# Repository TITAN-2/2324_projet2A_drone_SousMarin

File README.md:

# Projet de Drone Sous-marin - TITAN II - 2e Année ENSEA

## Description du Projet

Ce projet de deuxième année d'école d'ingénieur en électronique informatique vise à concevoir et développer un drone sous-marin contrôlable à distance. L'objectif de ce projet est de récupérer des objets dans le fond de l'étang de Cergy : plus précisement des lunettes de plongée. 
Le drone sera équipé de deux moteurs submersibles afin de propulser l'ensemble sous l'eau, de différents capteurs explicités plus tard, de seringues en guise de ballast, et finalement d'une STM32 couplée a une Raspeberry Pi. 

Le drone sera équipé de capteurs de pression et d'une centrale inertielle, connectés à une carte STM32. La communication entre les capteurs, les moteurs et les utilisateurs sera gérée par la STM32, tandis qu'une Raspberry Pi sera utilisée pour recevoir les informations des utilisateurs, héberger un serveur, et afficher une interface homme-machine (IHM) avec un flux vidéo provenant des caméras Pi.

## Fonctionnalités Principales

1. **STM32 pour la Gestion des Capteurs et des Moteurs**
   - La carte STM32 sera responsable de la communication avec les capteurs.
   - Elle assurera également le contrôle des moteurs en réponse aux commandes des utilisateurs.

2. **Raspberry Pi pour l'Interface Utilisateur**
   - La Raspberry Pi recevra les informations des utilisateurs.
   - Elle hébergera un serveur qui affichera le flux vidéo des caméras Pi et permettra aux utilisateurs d'envoyer des commandes au drone sous-marin.

3. **UART STM32 et la Raspberry Pi**
   - L'UART sera bidirectionnel
   - La Rasberry communiquera vers la STM32 les commandes utilisateurs reçu du serveur.
   - La STM32 communiquera vers la Raspberry les informations des différents capteurs (position, vitesse, niveau de batterie...)

## Configuration Matérielle

- **STM32**
  - Pin A0: PWM Moteur Gauche
  - Pin A1: PWM Moteur Droit
  - Pin RX: Reception de l'UART Raspberry
  - Pin TX: Transmission via UART vers Raspberry

- **Raspberry Pi**
  - A définir

- **Caméras Pi**
  - Voir le HowTo (a définir également)

## Installation et Exécution

1. Cloner le dépôt du projet sur la machine hôte.
   ```bash
   git clone https://github.com/votre-utilisateur/projet-drone-sous-marin.git
## Tester les parties indépendemments

[LA RECEPTION STM32](/RECEPTION_UART_H7A3ZIQ/HOWTO.md)

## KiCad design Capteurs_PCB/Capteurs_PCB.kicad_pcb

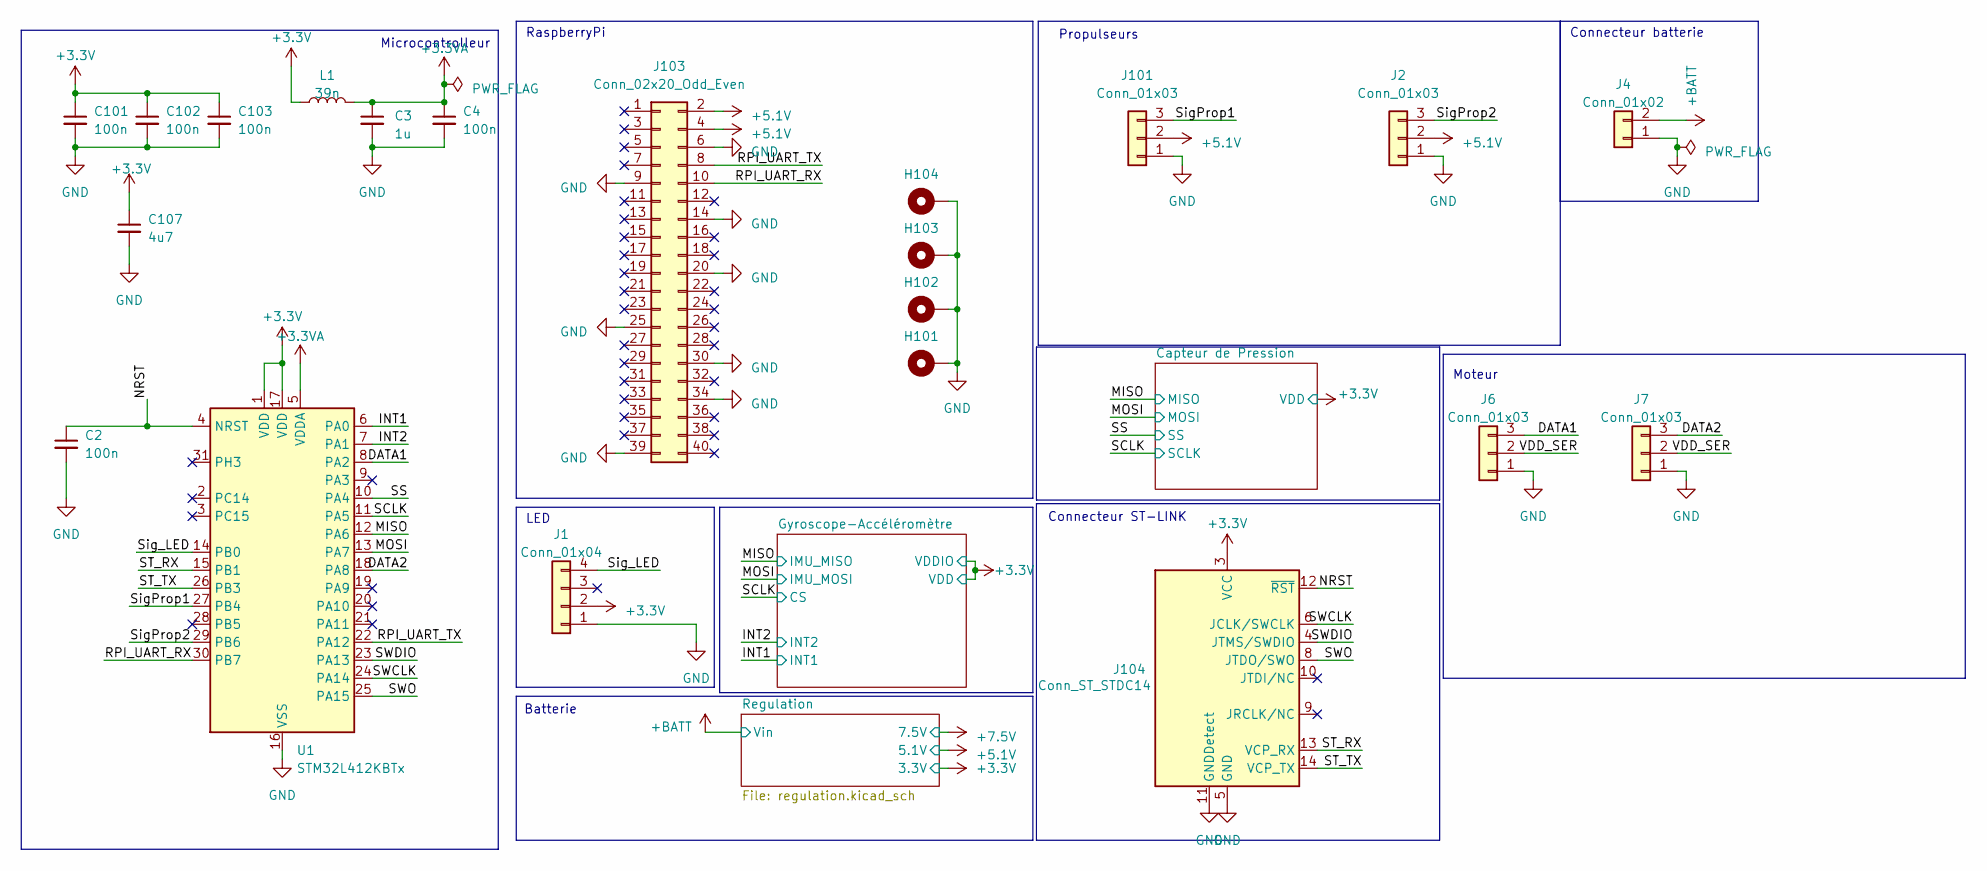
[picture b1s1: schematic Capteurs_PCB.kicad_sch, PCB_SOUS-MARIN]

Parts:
C2, C4, C101, C102, C103: 100n; C_0603_1608Metric_Pad1.08x0.95mm_HandSolder
C3: 1u; C_0603_1608Metric_Pad1.08x0.95mm_HandSolder
C107: 4u7; C_0603_1608Metric_Pad1.08x0.95mm_HandSolder
H101, H102, H103, H104: MountingHole_Pad; MountingHole_3.2mm_M3_DIN965_Pad
J1: Conn_01x04; JST_XH_B4B-XH-A_1x04_P2.50mm_Vertical
J2, J6, J7, J101: Conn_01x03; JST_XH_B3B-XH-A_1x03_P2.50mm_Vertical
J4: Conn_01x02; AMASS_XT60-M_1x02_P7.20mm_Vertical
J103: Conn_02x20_Odd_Even; PinSocket_2x20_P2.54mm_Vertical
J104: Conn_ST_STDC14; PinHeader_2x07_P1.27mm_Vertical_SMD
L1: 39n; L_0805_2012Metric_Pad1.05x1.20mm_HandSolder
U1: STM32L412KBTx; LQFP-32_7x7mm_P0.8mm

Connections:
+3.3V: C101.1, C102.1, C103.1, C107.1, J1.2, J104.3 (VCC), L1.1, U1.1 (VDD), U1.17 (VDD); also elsewhere on the board
+3.3VA: C3.1, C4.1, L1.2, U1.5 (VDDA)
+5V: J2.2, J101.2, J103.2, J103.4; also elsewhere on the board
+BATT: J4.2; also elsewhere on the board
/DATA1: J6.3, U1.8 (PA2)
/DATA2: J7.3, U1.18 (PA8)
/INT1: U1.6 (PA0); also elsewhere on the board
/INT2: U1.7 (PA1); also elsewhere on the board
/MISO: U1.12 (PA6); also elsewhere on the board
/MOSI: U1.13 (PA7); also elsewhere on the board
/NRST: C2.1, J104.12 (~RST), U1.4 (NRST)
/RPI_UART_RX: J103.10, U1.30 (PB7)
/RPI_UART_TX: J103.8, U1.22 (PA12)
/SCLK: U1.11 (PA5); also elsewhere on the board
/SS: U1.10 (PA4); also elsewhere on the board
/ST_RX: J104.13 (VCP_RX), U1.15 (PB1)
/ST_TX: J104.14 (VCP_TX), U1.26 (PB3)
/SWCLK: J104.6 (JCLK/SWCLK), U1.24 (PA14)
/SWDIO: J104.4 (JTMS/SWDIO), U1.23 (PA13)
/SWO: J104.8 (JTDO/SWO), U1.25 (PA15)
/SigProp1: J101.3, U1.27 (PB4)
/SigProp2: J2.3, U1.29 (PB6)
/Sig_LED: J1.4, U1.14 (PB0)
/VDD_SER: J6.2, J7.2
GND: C2.2, C3.2, C4.2, C101.2, C102.2, C103.2, C107.2, H101.1, H102.1, H103.1, H104.1, J1.1, J2.1, J4.1, J6.1, J7.1, J101.1, J103.6, J103.9, J103.14, J103.20, J103.25, J103.30, J103.34, J103.39, J104.5 (GND), J104.7 (GND), J104.11 (GNDDetect), U1.16 (VSS), U1.32 (VSS); also elsewhere on the board

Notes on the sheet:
Microcontrolleur
Batterie
Moteur
Connecteur batterie
LED
Connecteur ST-LINK
RaspberryPi
Propulseurs

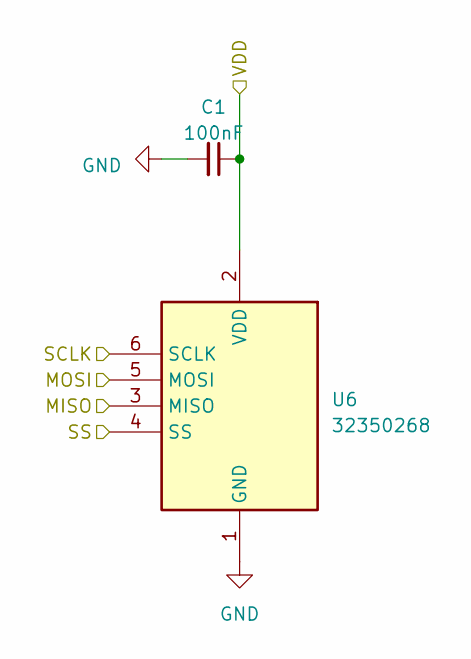
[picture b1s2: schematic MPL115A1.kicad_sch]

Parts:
C1: 100nF; C_0603_1608Metric_Pad1.08x0.95mm_HandSolder
U6: 32350268; Pressure_Captor_Custom

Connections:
+3V3: C1.1, U6.2 (VDD); also elsewhere on the board
/MISO: U6.3 (MISO); also elsewhere on the board
/MOSI: U6.5 (MOSI); also elsewhere on the board
/SCLK: U6.6 (SCLK); also elsewhere on the board
/SS: U6.4 (SS); also elsewhere on the board
GND: C1.2, U6.1 (GND); also elsewhere on the board

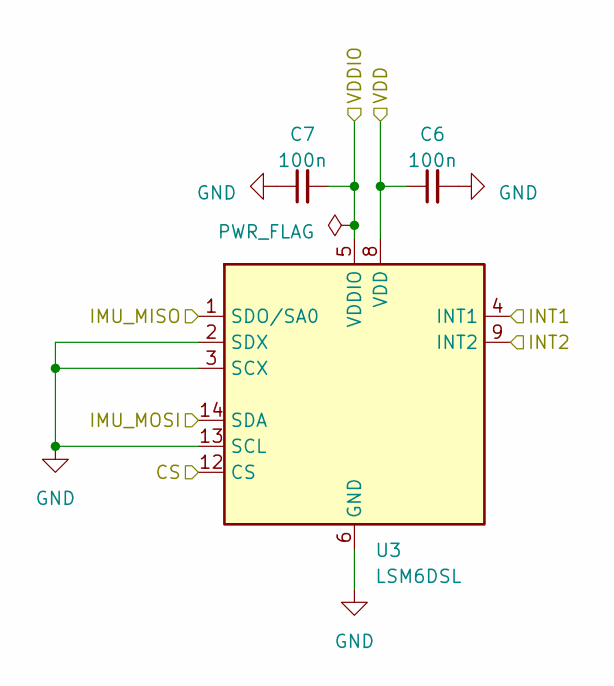
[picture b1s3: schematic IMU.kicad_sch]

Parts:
C6, C7: 100n; C_0603_1608Metric_Pad1.08x0.95mm_HandSolder
U3: LSM6DSL; LGA-14_3x2.5mm_P0.5mm_LayoutBorder3x4y

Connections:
+3V3: C6.1, C7.2, U3.5 (VDDIO), U3.8 (VDD); also elsewhere on the board
/INT1: U3.4 (INT1); also elsewhere on the board
/INT2: U3.9 (INT2); also elsewhere on the board
/MISO: U3.1 (SDO/SA0); also elsewhere on the board
/MOSI: U3.14 (SDA); also elsewhere on the board
/SCLK: U3.12 (CS); also elsewhere on the board
GND: C6.2, C7.1, U3.2 (SDX), U3.3 (SCX), U3.6 (GND), U3.7 (GND), U3.13 (SCL); also elsewhere on the board

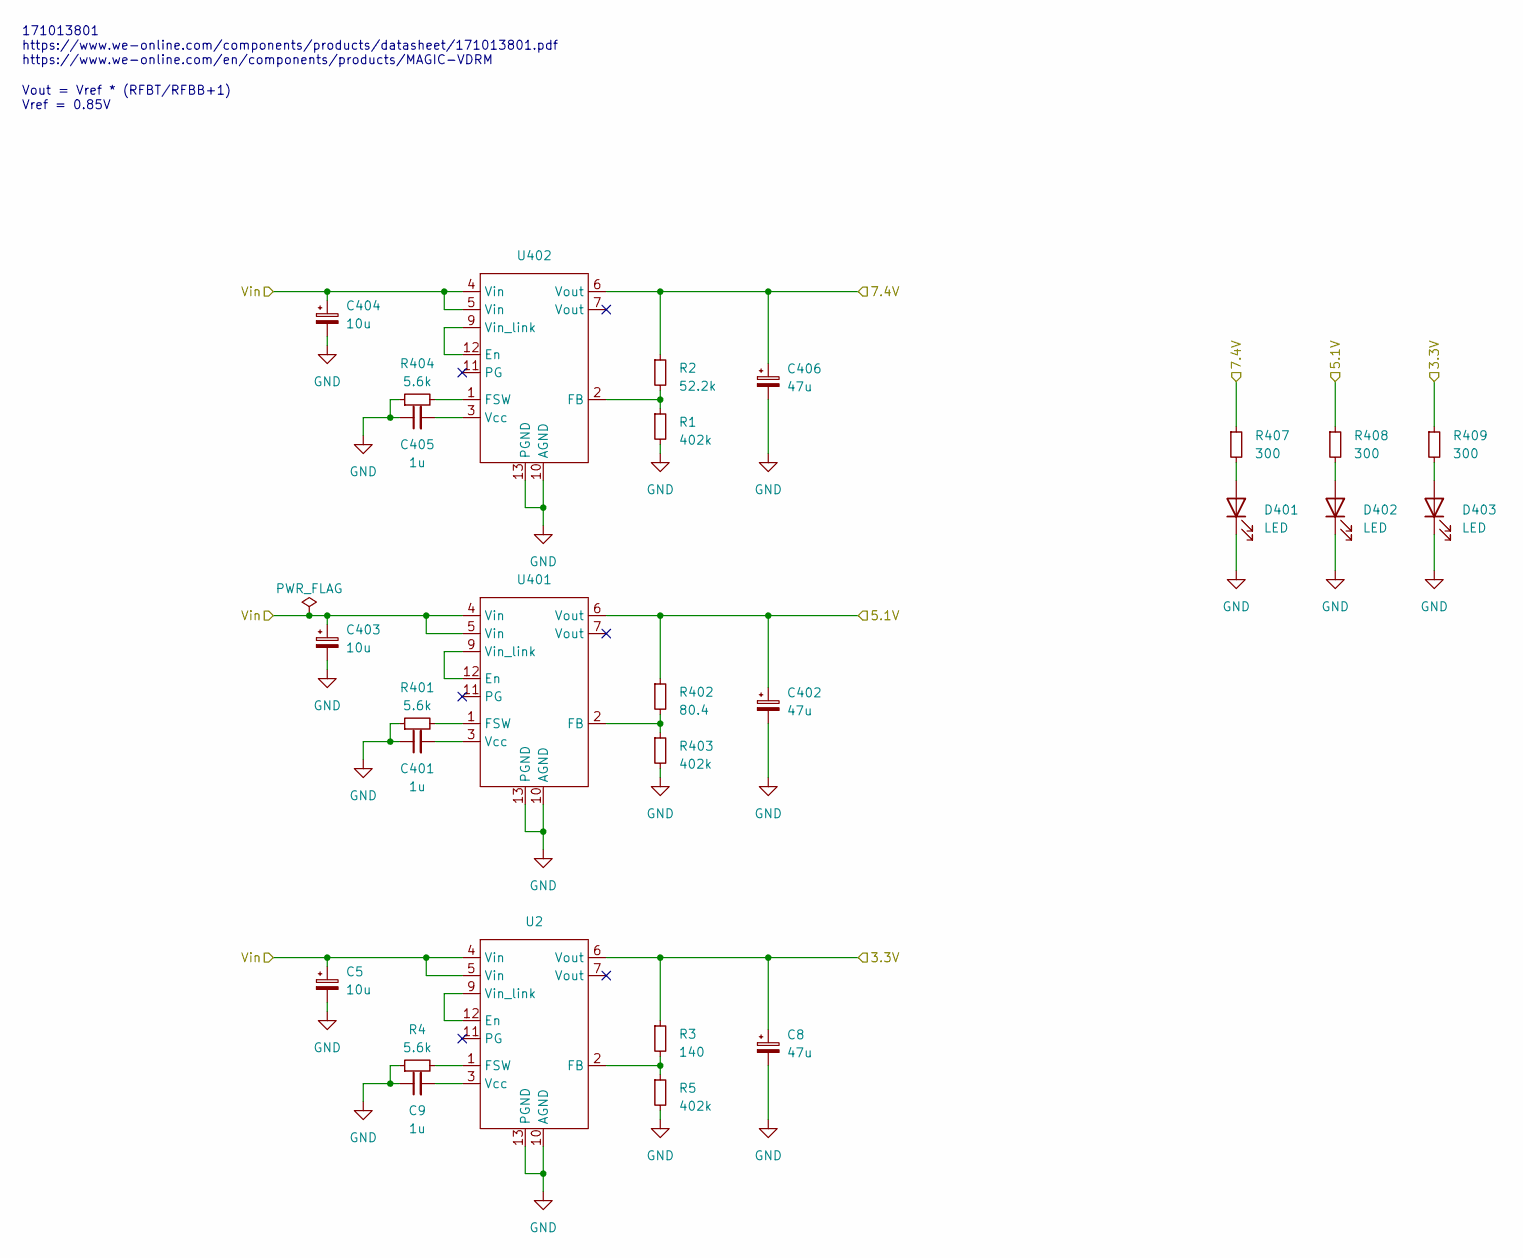
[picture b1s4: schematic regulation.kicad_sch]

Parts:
C5, C403, C404: 10u; CP_Elec_5x5.4; MPN 865060542002
C8, C402, C406: 47u; CP_Elec_6.3x5.4; MPN 865060543005
C9, C401, C405: 1u; C_0603_1608Metric_Pad1.08x0.95mm_HandSolder
D401, D402, D403: LED; LED_D5.0mm_Clear
R1, R5, R403: 402k; R_0603_1608Metric_Pad0.98x0.95mm_HandSolder
R2: 52.2k; R_0603_1608Metric_Pad0.98x0.95mm_HandSolder
R3: 140; R_0603_1608Metric_Pad0.98x0.95mm_HandSolder
R4, R401, R404: 5.6k; R_0603_1608Metric_Pad0.98x0.95mm_HandSolder
R402: 80.4; R_0603_1608Metric_Pad0.98x0.95mm_HandSolder
R407, R408, R409: 300; R_0603_1608Metric_Pad0.98x0.95mm_HandSolder
U2, U401, U402: Regulator; MPN 171013801

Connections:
+3.3V: C8.1, R3.1, R409.1, U2.6 (Vout); also elsewhere on the board
+5V: C402.1, R402.1, R408.1, U401.6 (Vout); also elsewhere on the board
+7.5V: C406.1, R2.1, R407.1, U402.6 (Vout)
+BATT: C5.1, C403.1, C404.1, U2.4 (Vin), U2.5 (Vin), U401.4 (Vin), U401.5 (Vin), U402.4 (Vin), U402.5 (Vin); also elsewhere on the board
GND: C5.2, C8.2, C9.1, C401.1, C402.2, C403.2, C404.2, C405.1, C406.2, D401.1 (K), D402.1 (K), D403.1 (K), R1.2, R4.1, R5.2, R401.1, R403.2, R404.1, U2.10 (AGND), U2.13 (PGND), U401.10 (AGND), U401.13 (PGND), U402.10 (AGND), U402.13 (PGND); also elsewhere on the board
unnamed: D401.2 (A), R407.2
unnamed: D402.2 (A), R408.2
unnamed: D403.2 (A), R409.2
unnamed: U2.9 (Vin_link), U2.12 (En)
unnamed: R3.2, R5.1, U2.2 (FB)
unnamed: R4.2, U2.1 (FSW)
unnamed: C9.2, U2.3 (Vcc)
unnamed: U401.9 (Vin_link), U401.12 (En)
unnamed: R402.2, R403.1, U401.2 (FB)
unnamed: R401.2, U401.1 (FSW)
unnamed: C401.2, U401.3 (Vcc)
unnamed: U402.9 (Vin_link), U402.12 (En)
unnamed: R1.1, R2.2, U402.2 (FB)
unnamed: R404.2, U402.1 (FSW)
unnamed: C405.2, U402.3 (Vcc)

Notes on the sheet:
Vout = Vref * (RFBT/RFBB+1) Vref = 0.85V
171013801 https://www.we-online.com/components/products/datasheet/171013801.pdf https://www.we-online.com/en/components/products/MAGIC-VDRM

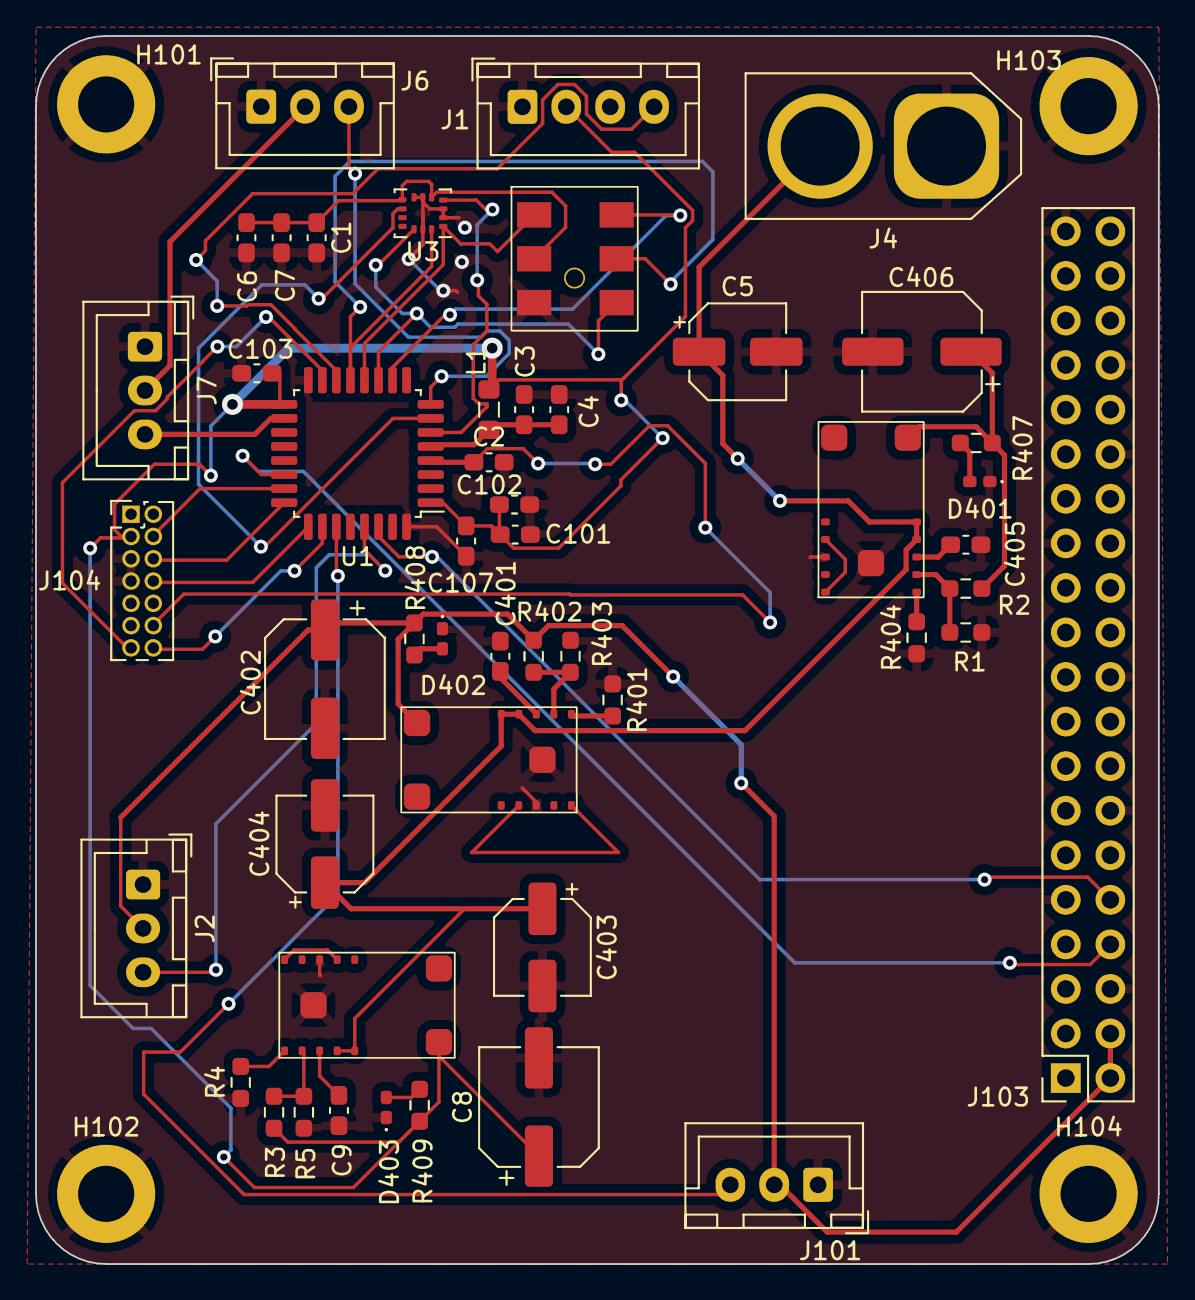
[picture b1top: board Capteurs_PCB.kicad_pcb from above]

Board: 2 copper layers, 64.0 x 70.0 mm, 53 parts (0 on the bottom side), 42 nets.

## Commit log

2023-09-26 brainstorm
2023-09-26 Commit cahier des charges
2023-09-26 Create Liste matériaux
2023-09-26 Commit pour le Diaporama
2023-09-26 Update Liste matériaux
2023-10-03 Update Datasheet
2023-10-03 Update liste matériaux et ajout du diagramme d'archi
2023-10-10 update journal semaine 3
2023-10-17 Diagramme D'archi .pptx
2023-10-17 Update diagramme d'archi 2
2023-11-07 Update Journal de bord
2023-11-14 ajout du dossier flux video
2023-11-15 [V1] Creation of README.md
    Explication brève du projet
2023-11-28 Maquette Figma pour l'intefrace H/M
    Ajout de la maquette qui dispose tous les éléments présents, cela facilitera la partie code HTML/CSS
2023-11-28 Add STM32 Thrust Change
    Ajout du projet STM32CubeIde permettant la modification de la puissance des moteurs
2023-11-28 Ajout d'une partie du code pour la réception
    Il manque la partie de décodage pour affecter au bonne fonction les bonnes valeurs
2023-12-05 Réorga
2023-12-05 Control
2023-12-05 2 styles de joysticks
2023-12-05 modif Controls
2023-12-05 Code Flux video
    Code permettant de générer un flux vidéo (plutôt un flux de mjpg compressés) ayant pour adresse internet: 192.168.0.252:8000
2023-12-05 update joysticks
2023-12-05 Ajout code stm32 Reception | Delete old Stm32 Reception | Organize Send Raspberry
2023-12-12 updates Controls
2023-12-12 Update Control.html en intégrant les codes css et javascript
2023-12-12 Update interface HM
2024-01-16 Début PCB
2024-01-16 Reception STM32
    Possible maintenant de recevoir un signal de la Raspberry et de le print sur un Serial Plotter
2024-01-17 RPICom
2024-01-17 update code rpi com
2024-01-17 Rename HOWTO.md to README.md
2024-01-22 update kicad
2024-01-22 Avancement Process STM32
2024-01-22 Avancement sur la partie process
2024-01-23 Modification PCB
2024-01-23 PCB changement
    Pcb changé (Raspberry))
2024-01-23 Datasheet
    Datasheet des capteurs et de la STM32 utilisés pour le PCB
2024-01-23 pcb update
2024-01-24 uptdate PCB
2024-01-30 Raspberry UPDATE
2024-01-30 readSend
2024-01-30 updates pcb
2024-02-05 Modif seringues pcb
2024-02-06 [Working] STM32 Process
2024-02-06 modif kicad
2024-02-06 update pcb
2024-02-06 Factorisation de la V1 + Ajout d'un test UART
2024-02-06 Modif PCB
2024-02-14 Petites modifications erreurs sur PCB
2024-02-17 updates kicad
2024-02-17 kicad changes and starting footprints
2024-02-26 Changement pour éviter de tout casser
2024-02-26 Changement interrupteur
2024-02-26 ST-LINK sur Kicad
2024-02-27 Enlever les erreurs Kicad+Mettre connecteur batterie
2024-02-27 Kicad
2024-03-03 Empreintes
    A revoir car pas sur pour certaines + faire celles des composants modifiés
2024-03-05 Empreintes modifiées
2024-03-05 Footprint design and Footprint assignment
2024-03-05 Start routage
2024-03-05 Update routage
2024-03-05 Routage en cours
2024-03-07 Suite placement des composants pour routage
2024-03-07 Suite
2024-03-11 Début de routage
2024-03-12 modifs kicad
2024-03-12 Problème réglé
2024-03-12 Changement Label
2024-03-12 Suite PCB
2024-03-12 Ajout des requetes pour sendUart
2024-03-13 Add POE Injector
2024-03-13 Update control_V2
2024-03-13 Reorganisation github
2024-03-13 Routage
2024-03-14 Le routage continue
2024-03-17 Avancement PCB mais encore des problèmes
2024-03-18 Derniers changements mais encore des erreurs
2024-03-19 Pilotage des moteurs par joysticks [Fonctionnel]
2024-03-19 Ajout de l'envoie des données STM32
2024-03-19 Petit changement
    Explication du dernier commit:
    -Création d'un TIM3 cadencé a 1 Hz
    -Interrutpion TIM3 : envoie des données en uart des data Capteurs
    -Aucun capteur pour le moment on simule avec de fausses
    -Création du RPICom_SendBinaryMessage qui envoie vers Rasberry le bon format de donnée + vers huartDebug
2024-03-19 Adding Code for the map
2024-03-20 modif JS map
2024-03-26 update static
2024-03-26 Modification du PCB
2024-03-26 Correction des interruptions TIM3
2024-03-26 Receive uart and updates on web
2024-03-26 XL320 Tournant
2024-03-26 Ajout du AdjustDepth par le XL
2024-03-28 Fonctionnement des seringues avec XML320 !
2024-03-28 Git reorganisation
2024-04-01 Finition et plus d'erreur sur le PCB
2024-04-02 Tentative XL Mode Wheel
2024-04-02 update raspberry
